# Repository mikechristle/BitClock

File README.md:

# BitClock
How can I display the time. Let me count the ways.  

Over the years I have built several clock projects to display the time in interesting ways.
Most have had limited success because of the challenge of keeping accurate time.
This clock uses a Raspberry Pi Pico W to get the correct time over the internet.
This is definitely overkill for a clock, but at $6 I said why not.
## Overview
A clock that displays the time in binary.  
  
The display has three rows of four LEDs.
The top row displays the hour, 1 to 12.
The middle row displays the tens of minutes, 0 to 5.
The bottom row displays the ones of minutes, 0 to 9.  

The clock has a buzzer to play a song for an alarm.
To set the alarm time, use the PC Control Program.
## Code
The BitClock is controlled by a Raspberry Pi Pico W.
All the code is written in Micro-Python.
The code will get the current time over the internet using the get_ntp_time library.

The file network.info contains the login credentials for you router.
When the clock powers up, it will use this info to login, 
then display the last byte of the IP address for 10 seconds.
This address is needed in the PS control program to connect to the clock.
## PC Control Program
The control program was written in Python.
It runs on a PC and communicates with the clock with a socket connection.
I tested is on Windows, since it is Python it should run on Apple and Linux.
This program will allow you to set the alarm, set the time zone,
and adjust the LED brightness.
## PCB
The PCB was designed in KiCad version 10.0.1.
It is a two layer board.
All of the symbol and footprints are included in the local definition files.

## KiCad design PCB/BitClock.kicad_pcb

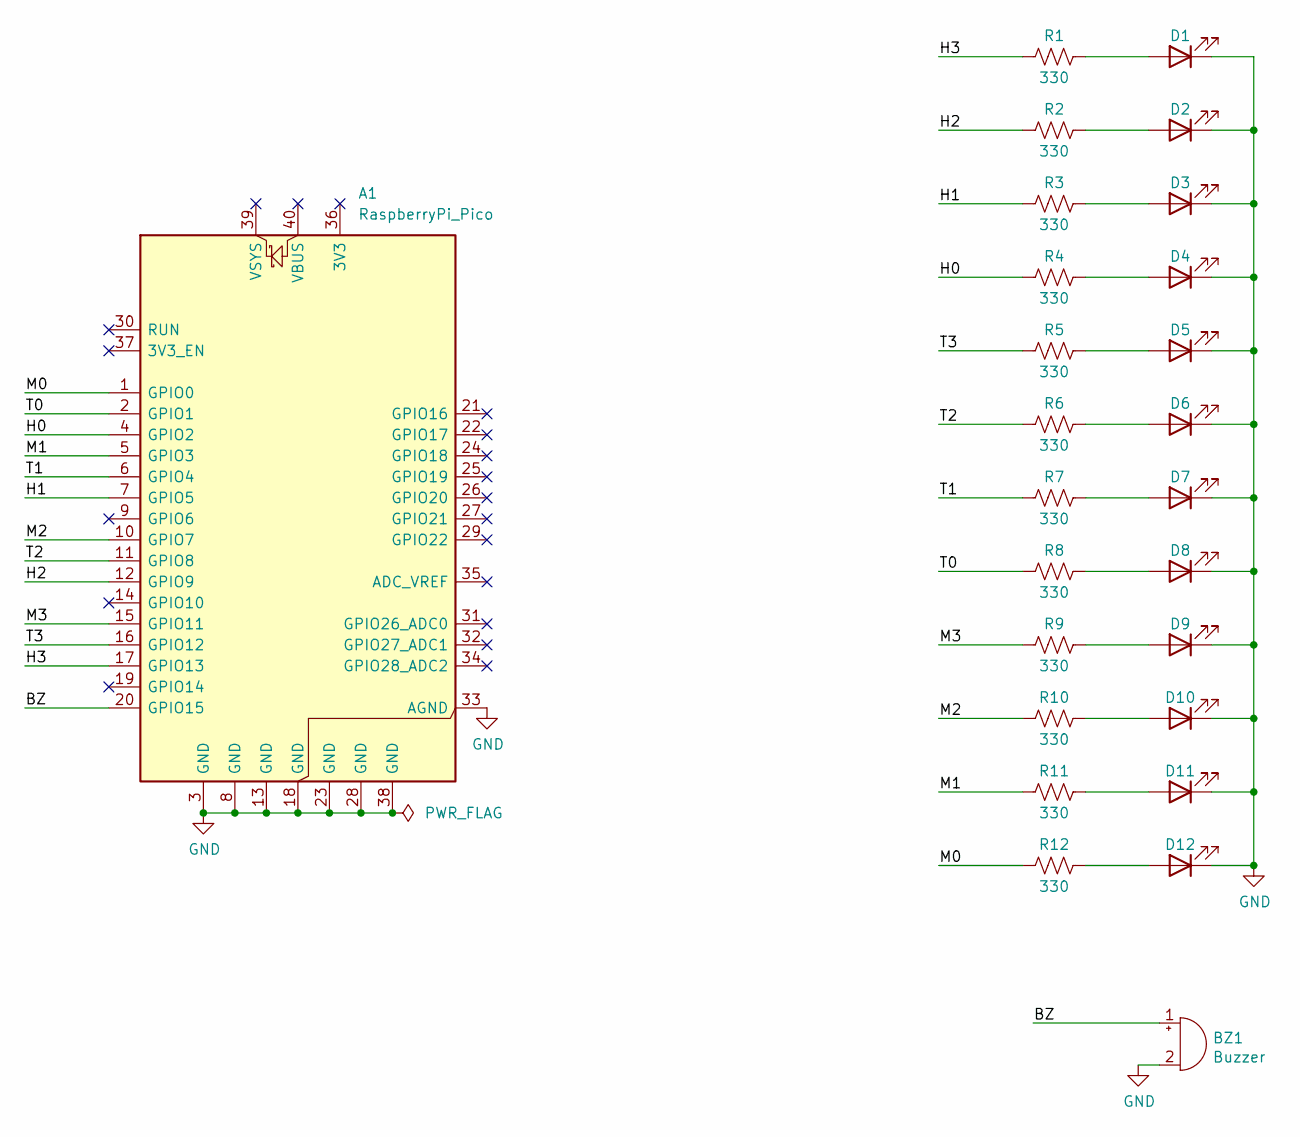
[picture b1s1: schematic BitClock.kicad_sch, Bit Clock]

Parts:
A1: RaspberryPi_Pico; DIP-40_700_ELL
BZ1: Buzzer; Buzzer_D14mm_H7mm_P10mm
D1, D2, D3, D4, D5, D6, D7, D8, D9, D10, D11, D12: LED; LED_D8.0mm
R1, R2, R3, R4, R5, R6, R7, R8, R9, R10, R11, R12: 330; R_Axial_DIN0204_L3.6mm_D1.6mm_P5.08mm_Horizontal

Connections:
/BZ: A1.20 (GPIO15), BZ1.1 (+)
/H0: A1.4 (GPIO2), R4.2
/H1: A1.7 (GPIO5), R3.2
/H2: A1.12 (GPIO9), R2.2
/H3: A1.17 (GPIO13), R1.2
/M0: A1.1 (GPIO0), R12.2
/M1: A1.5 (GPIO3), R11.2
/M2: A1.10 (GPIO7), R10.2
/M3: A1.15 (GPIO11), R9.2
/T0: A1.2 (GPIO1), R8.2
/T1: A1.6 (GPIO4), R7.2
/T2: A1.11 (GPIO8), R6.2
/T3: A1.16 (GPIO12), R5.2
GND: A1.3 (GND), A1.8 (GND), A1.13 (GND), A1.18 (GND), A1.23 (GND), A1.28 (GND), A1.33 (AGND), A1.38 (GND), BZ1.2 (-), D1.1 (K), D2.1 (K), D3.1 (K), D4.1 (K), D5.1 (K), D6.1 (K), D7.1 (K), D8.1 (K), D9.1 (K), D10.1 (K), D11.1 (K), D12.1 (K)
unnamed: D1.2 (A), R1.1
unnamed: D2.2 (A), R2.1
unnamed: D3.2 (A), R3.1
unnamed: D4.2 (A), R4.1
unnamed: D5.2 (A), R5.1
unnamed: D6.2 (A), R6.1
unnamed: D7.2 (A), R7.1
unnamed: D8.2 (A), R8.1
unnamed: D9.2 (A), R9.1
unnamed: D10.2 (A), R10.1
unnamed: D11.2 (A), R11.1
unnamed: D12.2 (A), R12.1

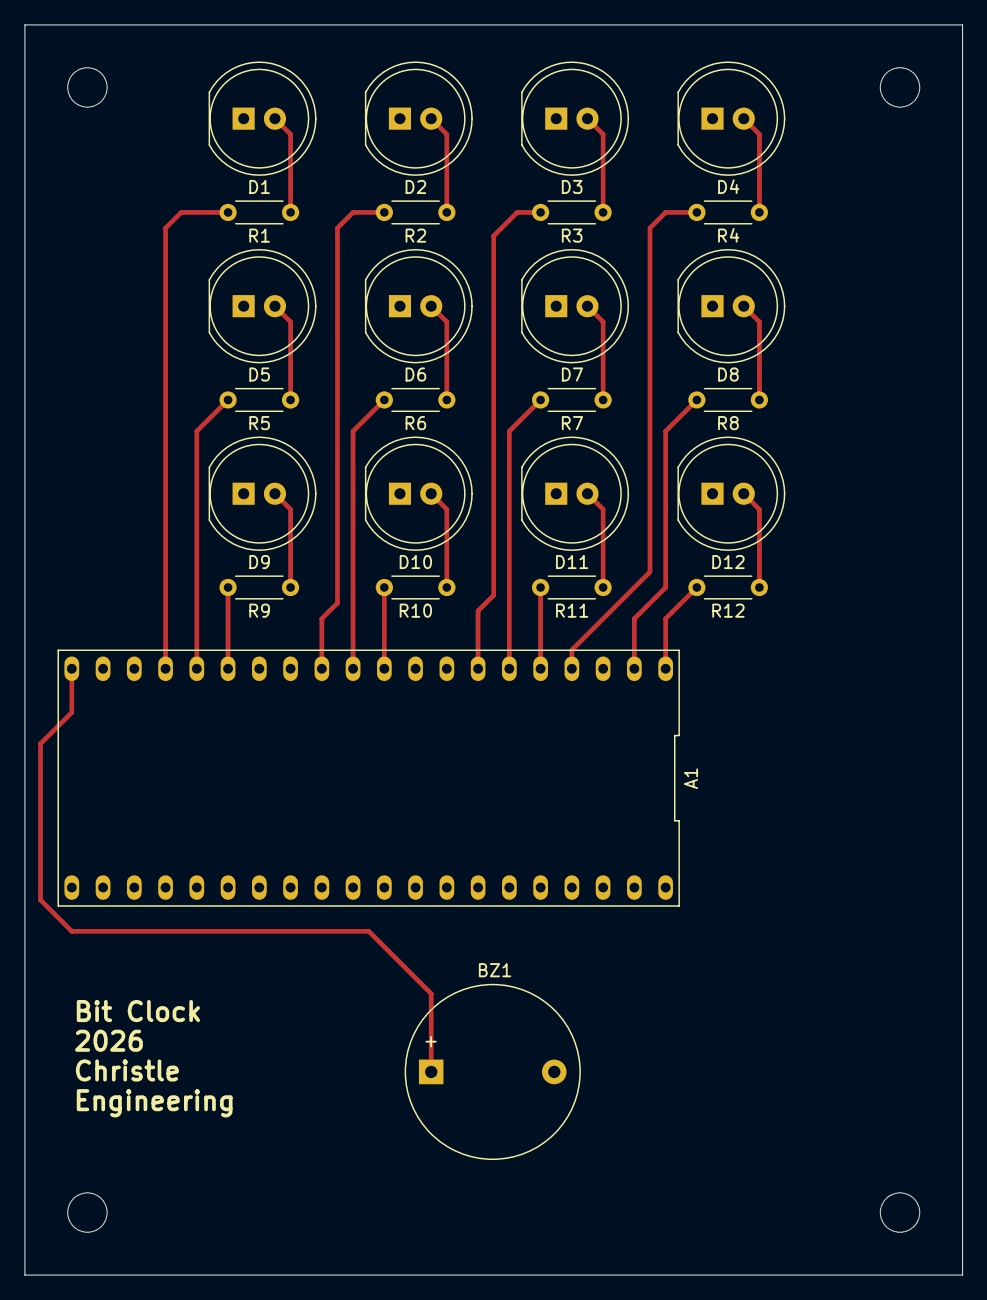
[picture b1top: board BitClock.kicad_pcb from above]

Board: 2 copper layers, 76.2 x 101.6 mm, 26 parts (0 on the bottom side), 26 nets.

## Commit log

2026-04-24 Update README.md
    Added info on network connection.
2026-04-24 Initial release.
2026-04-25 Update main.py
    Changed network.info to login.txt.
